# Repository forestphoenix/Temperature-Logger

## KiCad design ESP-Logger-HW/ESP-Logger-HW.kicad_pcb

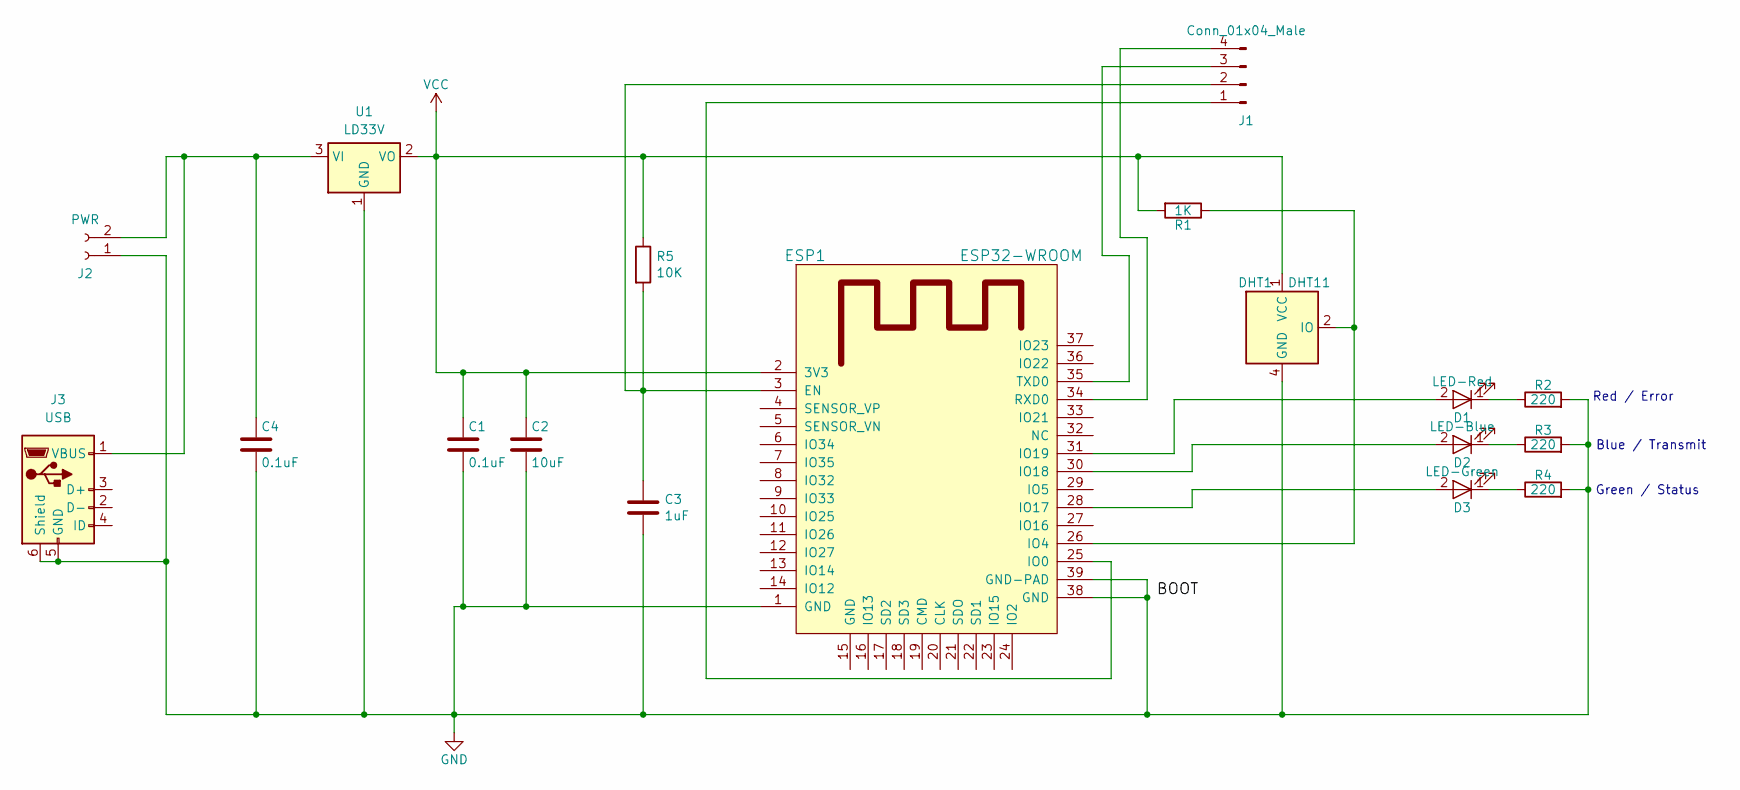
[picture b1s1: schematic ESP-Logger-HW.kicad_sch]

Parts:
C1, C4: 0.1uF; C_0603_1608Metric_Pad1.08x0.95mm_HandSolder; LCSC C1590
C2: 10uF; C_0603_1608Metric_Pad1.08x0.95mm_HandSolder; LCSC C76614
C3: 1uF; C_0603_1608Metric_Pad1.08x0.95mm_HandSolder; LCSC C106858
D1: LED-Red; LED_0603_1608Metric_Pad1.05x0.95mm_HandSolder; LCSC C2286
D2: LED-Blue; LED_0603_1608Metric_Pad1.05x0.95mm_HandSolder; LCSC C138541
D3: LED-Green; LED_0603_1608Metric_Pad1.05x0.95mm_HandSolder; LCSC C165982
DHT1: DHT11; Aosong_DHT11_5.5x12.0_P2.54mm
ESP1: ESP32-WROOM; LCSC C9900078140
J1: Conn_01x04_Male; JST_XH_B4B-XH-A_1x04_P2.50mm_Vertical
J2: PWR; JST_XH_B2B-XH-A_1x02_P2.50mm_Vertical
J3: USB; USB_Micro-B_Amphenol_10118194_Horizontal
R1: 1K; R_0603_1608Metric_Pad0.98x0.95mm_HandSolder; LCSC C2889391
R2, R3, R4: 220; R_0603_1608Metric_Pad0.98x0.95mm_HandSolder; LCSC C327834
R5: 10K; R_0603_1608Metric_Pad0.98x0.95mm_HandSolder; LCSC C862388
U1: LD33V; SOT-223-3_TabPin2; LCSC C92102

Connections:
GND: C1.2, C2.2, C3.2, C4.2, DHT1.4 (GND), ESP1.1 (GND), ESP1.38 (GND), ESP1.39 (GND-PAD), J2.1, J3.5 (GND), J3.6 (Shield), R2.2, R3.2, R4.2, U1.1 (GND)
unnamed: D1.2 (A), ESP1.31 (IO19)
unnamed: D1.1 (K), R2.1
unnamed: D2.2 (A), ESP1.30 (IO18)
unnamed: D2.1 (K), R3.1
unnamed: D3.2 (A), ESP1.28 (IO17)
unnamed: D3.1 (K), R4.1
unnamed: DHT1.2 (IO), ESP1.26 (IO4), R1.1
unnamed: C3.1, ESP1.3 (EN), J1.2, R5.2
unnamed: ESP1.25 (IO0), J1.1
unnamed: ESP1.34 (RXD0), J1.4
unnamed: ESP1.35 (TXD0), J1.3
unnamed: C4.1, J2.2, J3.1 (VBUS), U1.3 (VI)
VCC: C1.1, C2.1, DHT1.1 (VCC), ESP1.2 (3V3), R1.2, R5.1, U1.2 (VO)

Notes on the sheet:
Red / Error
Blue / Transmit
Green / Status

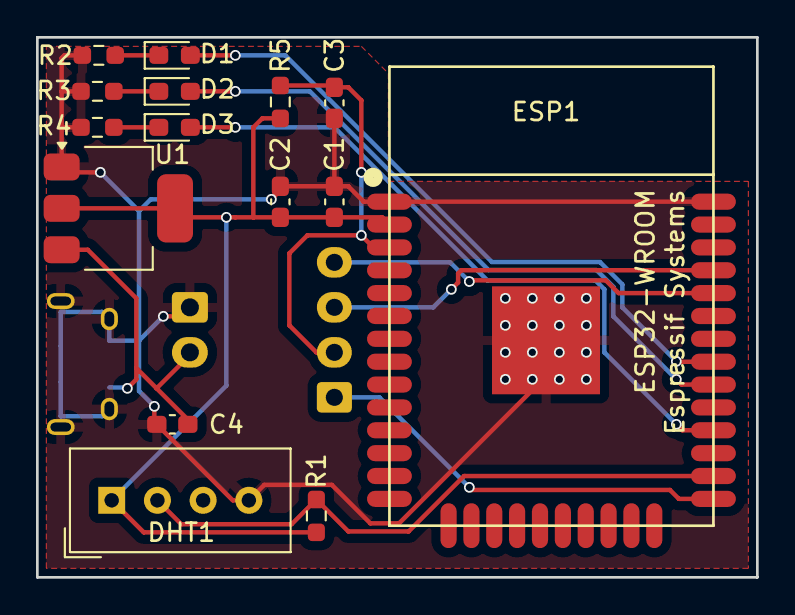
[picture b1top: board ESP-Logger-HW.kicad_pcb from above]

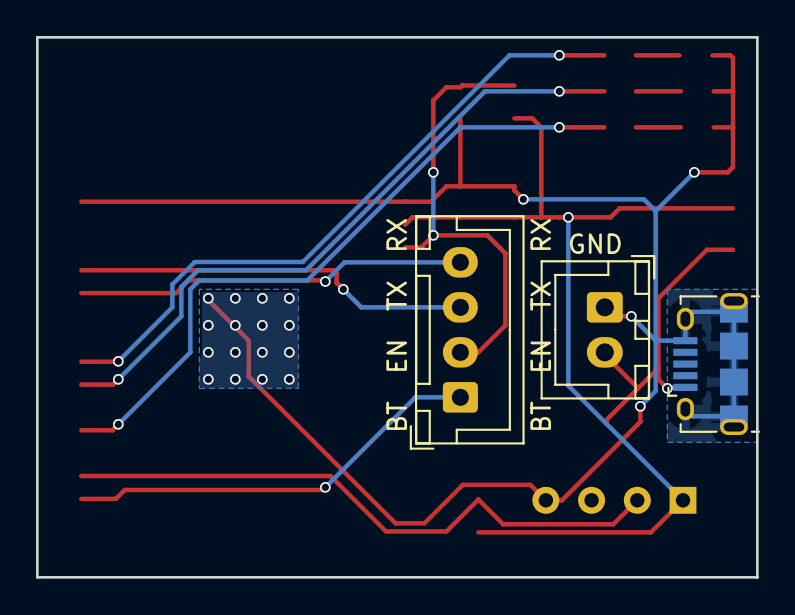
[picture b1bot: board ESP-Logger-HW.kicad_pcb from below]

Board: 2 copper layers, 40.0 x 30.0 mm, 18 parts (3 on the bottom side), 14 nets.

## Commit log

2020-10-08 Init repo with basic prototype
2020-11-23 Added the Hardware-Id to the data sent by the ESP32
2020-11-24 Added service discovery via mDNS
2020-11-24 Added new projects for Server & Hardware
2020-12-23 Added query to find out how long the sensors were running
2020-12-23 Added a simple interface to read the current temperature
2020-12-23 The ESP-Client now blinks when writing the temperature
2020-12-23 Update Haskell LTS
2020-12-23 Corrected a renaming in the transmission data structures
2021-02-17 First complete PCB
2021-03-16 Update the Pcb: Added the RC-Delay circuit that I forgot on the first prototype
2021-09-30 New 30x40 mm small Pcb layout
2024-05-24 server: Updated Db-Schema & Types
2024-05-24 server: add Containerfile
2024-05-24 Add Projects for the temperature-Logger ESP32 Firmware (+ Tests)
2024-05-24 Move (unfilled, not written) Webclient to Vue 3
2024-05-24 hardware: Update Circuit board, add Gerber files
2024-09-12 Update PCB and Gerber: Add USB power supply and voltage regulator
2024-09-12 Move project to package.yml, start dismantling database
2025-06-08 Firmware: Feat: Use MQTT for transmitting data, transmit on significant temperature or humidity changes
2025-06-17 Board: Move to SHT30 temperature sensor, add option for LC-Display
2025-06-17 templog-server: Bring App up-to-date, add a table output
2025-07-16 Feat(templog-server): Integrate a mqtt-worker into the templog-server
